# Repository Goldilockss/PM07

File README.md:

# PM07
Step-down circuit<br>
A board that functions like the Holybro Pixhawk 4 Power Module (PM07).

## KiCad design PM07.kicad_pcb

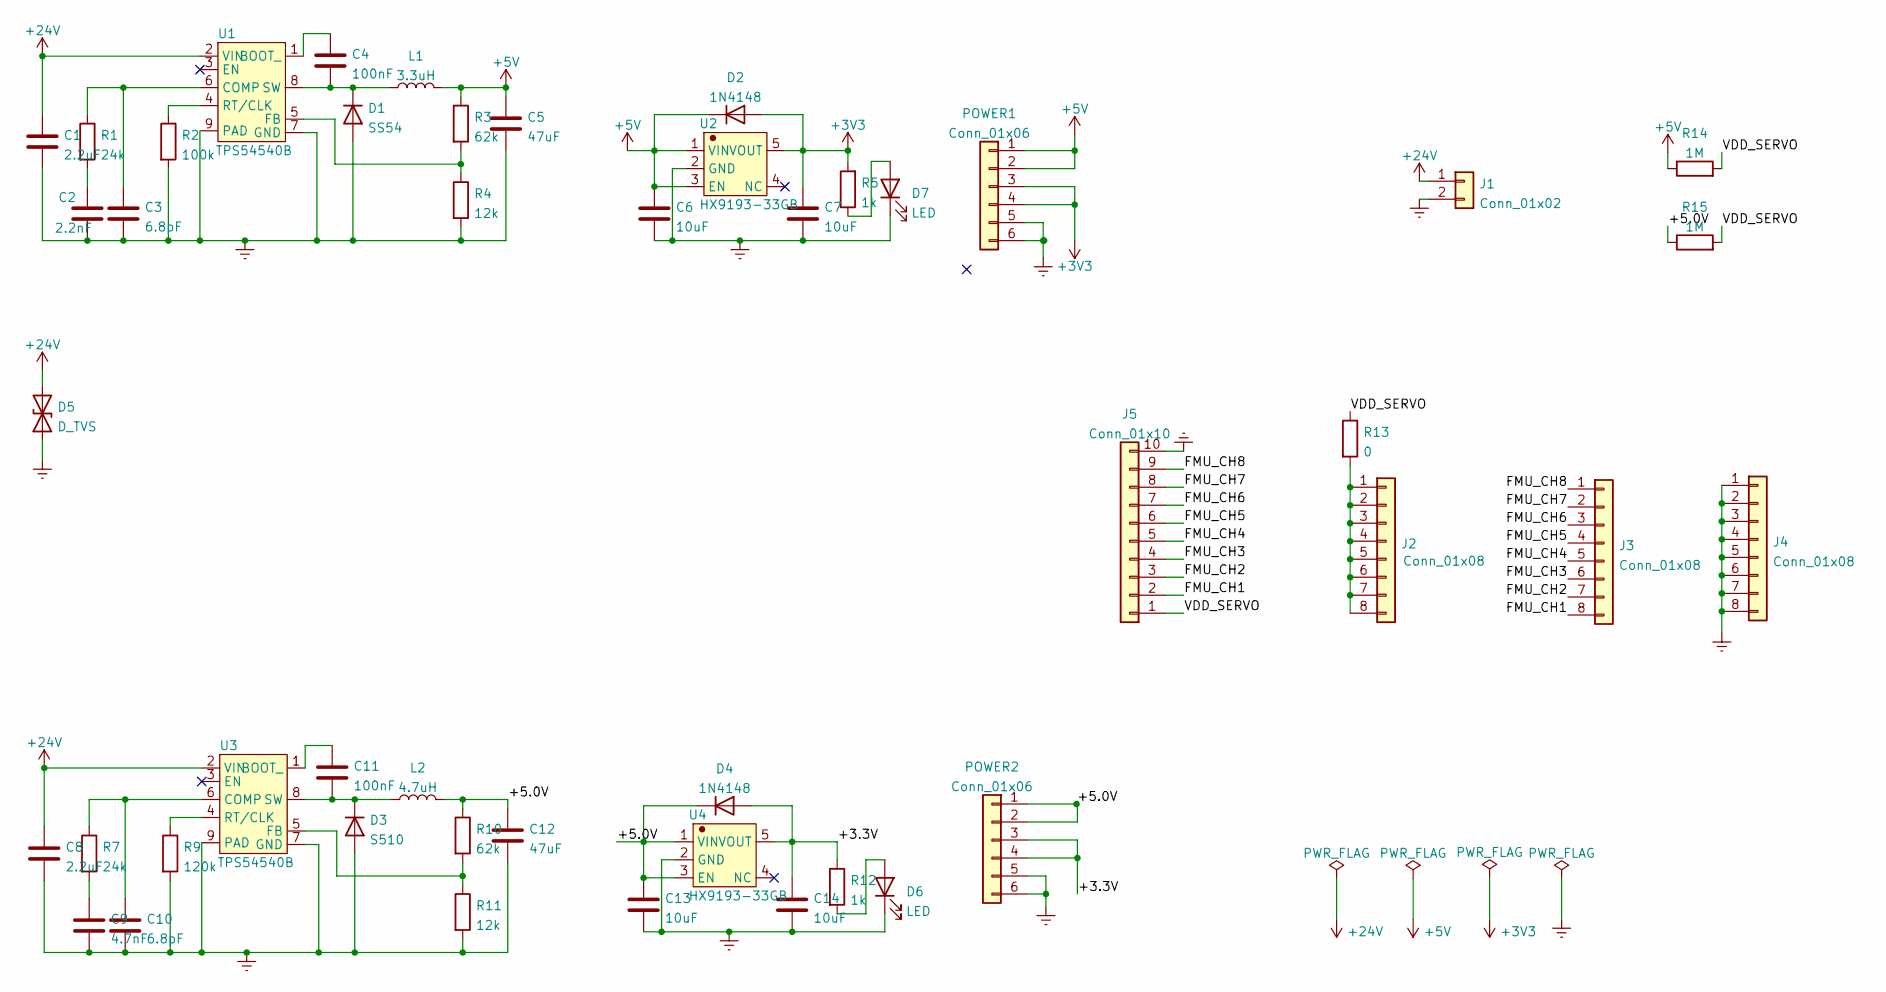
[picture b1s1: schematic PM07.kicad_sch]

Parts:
C1, C8: 2.2uF; C_1206_3216Metric_Pad1.33x1.80mm_HandSolder
C2: 2.2nF; C_0603_1608Metric_Pad1.08x0.95mm_HandSolder
C3, C10: 6.8pF; C_0603_1608Metric_Pad1.08x0.95mm_HandSolder
C4, C11: 100nF; C_0603_1608Metric_Pad1.08x0.95mm_HandSolder
C5, C12: 47uF; CP_Elec_5x5.4
C6, C7, C13, C14: 10uF; C_0603_1608Metric_Pad1.08x0.95mm_HandSolder
C9: 4.7nF; C_0603_1608Metric_Pad1.08x0.95mm_HandSolder
D1: SS54; D_SMA_Handsoldering
D2, D4: 1N4148; D_SOD-323_HandSoldering
D3: S510; D_SMA_Handsoldering
D5: D_TVS; D_SMB_Handsoldering
D6, D7: LED; LED_0603_1608Metric_Pad1.05x0.95mm_HandSolder
J1: Conn_01x02; AMASS_XT30U-M_1x02_P5.0mm_Vertical
J2, J3, J4: Conn_01x08; PinHeader_1x08_P2.54mm_Horizontal
J5: Conn_01x10; Molex_CLIK-Mate_502382-1070_1x10-1MP_P1.25mm_Vertical
L1: 3.3uH; L_7.3x7.3_H4.5
L2: 4.7uH; L_7.3x7.3_H4.5
POWER1, POWER2: Conn_01x06; Molex_CLIK-Mate_502382-0670_1x06-1MP_P1.25mm_Vertical
R1, R7: 24k; R_0603_1608Metric_Pad0.98x0.95mm_HandSolder
R2: 100k; R_0603_1608Metric_Pad0.98x0.95mm_HandSolder
R3, R10: 62k; R_0603_1608Metric_Pad0.98x0.95mm_HandSolder
R4, R11: 12k; R_0603_1608Metric_Pad0.98x0.95mm_HandSolder
R5, R12: 1k; R_0603_1608Metric_Pad0.98x0.95mm_HandSolder
R9: 120k; R_0603_1608Metric_Pad0.98x0.95mm_HandSolder
R13: 0; R_0603_1608Metric_Pad0.98x0.95mm_HandSolder
R14, R15: 1M; R_0603_1608Metric_Pad0.98x0.95mm_HandSolder
U1, U3: TPS54540B; SOIC-8-1EP_3.9x4.9mm_P1.27mm_EP2.29x3mm
U2, U4: HX9193-33GB; SOT-23-5_HandSoldering

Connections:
+3V3: C7.1, D2.2 (A), POWER1.3, POWER1.4, R5.2, U2.5 (VOUT)
+5V: C5.1, C6.1, D2.1 (K), L1.2, POWER1.1, POWER1.2, R3.1, R14.1, U2.1 (VIN), U2.3 (EN)
+24V: C1.1, C8.1, D5.2 (A2), J1.1, U1.2 (VIN), U3.2 (VIN)
/+3.3V: C14.1, D4.2 (A), POWER2.3, POWER2.4, R12.1, U4.5 (VOUT)
/+5.0V: C12.1, C13.1, D4.1 (K), L2.2, POWER2.1, POWER2.2, R10.1, R15.1, U4.1 (VIN), U4.3 (EN)
/FMU_CH1: J3.8, J5.2
/FMU_CH2: J3.7, J5.3
/FMU_CH3: J3.6, J5.4
/FMU_CH4: J3.5, J5.5
/FMU_CH5: J3.4, J5.6
/FMU_CH6: J3.3, J5.7
/FMU_CH7: J3.2, J5.8
/FMU_CH8: J3.1, J5.9
/VDD_SERVO: J5.1, R13.1, R14.2, R15.2
Earth: C1.2, C2.2, C3.2, C5.2, C6.2, C7.2, C8.2, C9.2, C10.2, C12.2, C13.2, C14.2, D1.2 (A), D3.2 (A), D5.1 (A1), D6.1 (K), D7.1 (K), J1.2, J4.1, J4.2, J4.3, J4.4, J4.5, J4.6, J4.7, J4.8, J5.10, POWER1.5, POWER1.6, POWER2.5, POWER2.6, R2.2, R4.2, R9.2, R11.2, U1.7 (GND), U1.9 (PAD), U2.2 (GND), U3.7 (GND), U3.9 (PAD), U4.2 (GND)
unnamed: C2.1, R1.2
unnamed: C3.1, R1.1, U1.6 (COMP)
unnamed: C4.1, U1.1 (BOOT_)
unnamed: C4.2, D1.1 (K), L1.1, U1.8 (SW)
unnamed: C9.1, R7.2
unnamed: C10.1, R7.1, U3.6 (COMP)
unnamed: C11.1, U3.1 (BOOT_)
unnamed: C11.2, D3.1 (K), L2.1, U3.8 (SW)
unnamed: D6.2 (A), R12.2
unnamed: D7.2 (A), R5.1
unnamed: J2.1, J2.2, J2.3, J2.4, J2.5, J2.6, J2.7, J2.8, R13.2
unnamed: R2.1, U1.4 (RT/CLK)
unnamed: R3.2, R4.1, U1.5 (FB)
unnamed: R9.1, U3.4 (RT/CLK)
unnamed: R10.2, R11.1, U3.5 (FB)

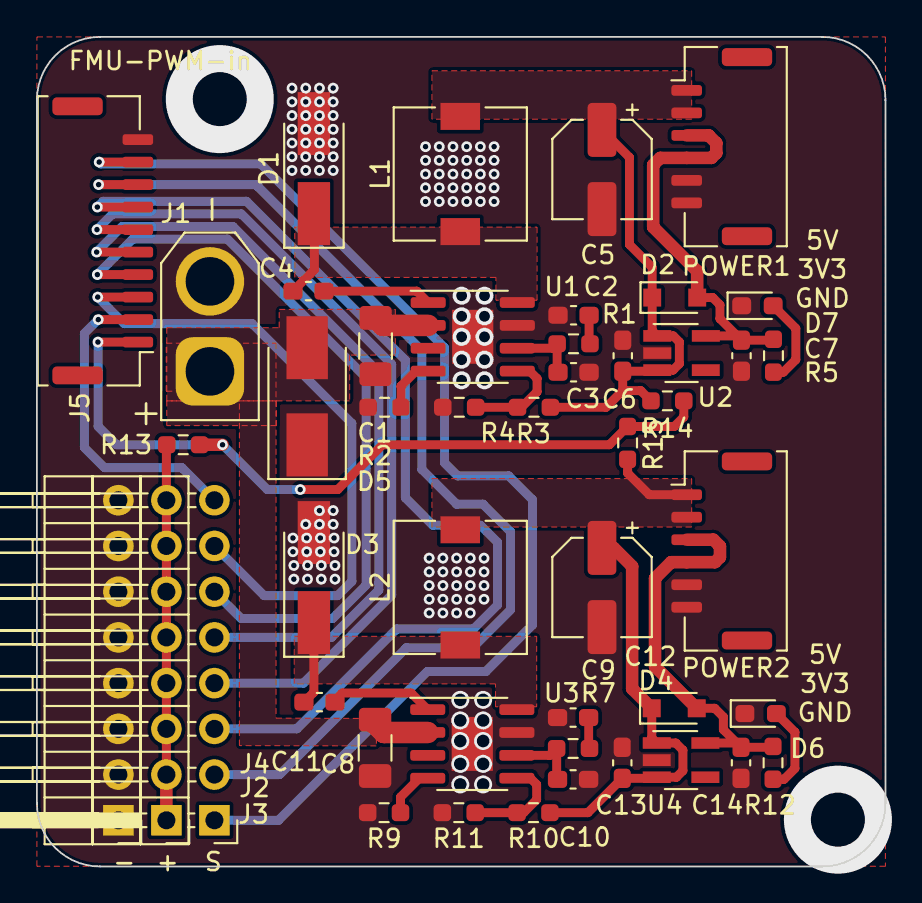
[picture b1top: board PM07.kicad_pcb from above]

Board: 2 copper layers, 47.1 x 46.1 mm, 47 parts (0 on the bottom side), 30 nets.

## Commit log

2023-04-02 master
